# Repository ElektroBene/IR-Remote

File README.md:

# IR-Remote
## Introduction
This is a project for the course "microelectrical systems and design" in the electrical engineering and computer science studies at the Aschaffenburg University of Applied Sciences. The project will contain schematics and assembly code to build a custom infrared remote with the standard RC5 protocol.

## Schematics
- v1: basic schematic to show inputs and outputs with pic18f452
- v2: proper schematic including reset circuit, quartz oscillator and power supply
- v3: proper layout with remote design
- v4: optimize inductor width, space management and add cooling area for power supply
- v5: reroute with pwm and interrupt pins, add cooling area for battery and gnd area

## Authors
Benedikt Schnörr,
Sebastian Pasinski

### Work Packages
- schematics in v1 and v2: Benedikt
- layout in v2: Sebastian
- schematics in v3: Benedikt, Sebastian
- layout in v3: Benedikt, Sebastian
- layout in v4/5: Benedikt
- code for rc5 protocol: Benedikt

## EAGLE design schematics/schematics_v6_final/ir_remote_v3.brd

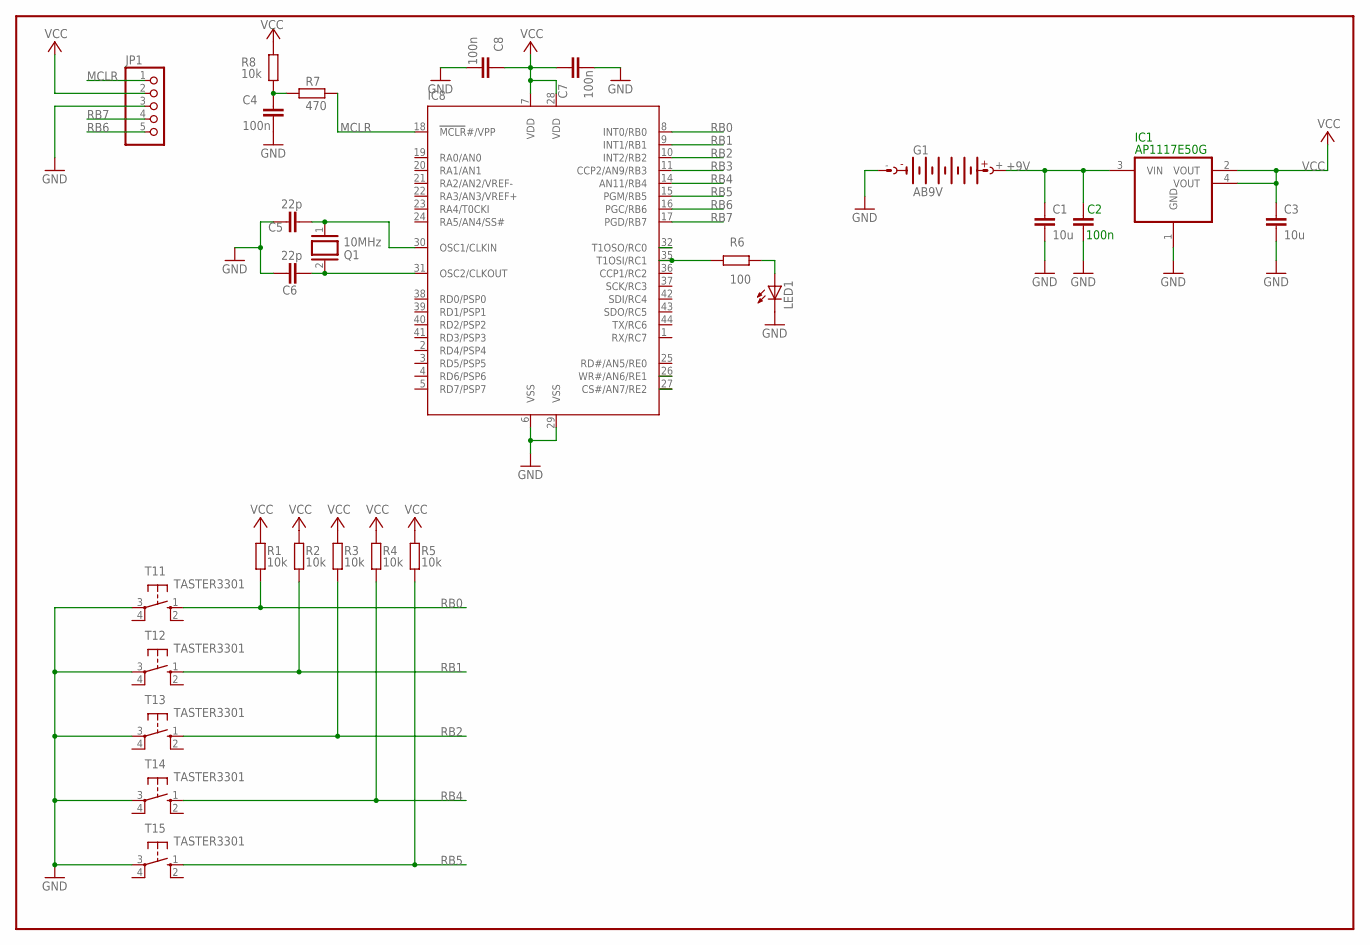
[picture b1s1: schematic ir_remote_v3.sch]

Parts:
C1, C3: 10u; C0805
C2, C4, C7, C8: 100n; C0805
C5, C6: 22p; C0603_WE
G1: AB9V
IC1: AP1117E50G; SOT223
IC8: PIC18F4520; TQFP44
JP1: PINHD-1X5; 1X05
LED1: LED5MM
Q1: 10MHz; QUARZ_HC5032/2
R1, R2, R3, R4, R5, R8: 10k; M0805
R6: 100; M0805
R7: 470; M0805
T11, T12, T13, T14, T15: TASTER3301

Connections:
+9V: C1.1, C2.1, G1.+, IC1.3 (VIN)
D0_LCD: IC8.27 (CS#/AN7/RE2)
D1_LCD: IC8.26 (WR#/AN6/RE1)
GND: C1.2, C2.2, C3.2, C4.2, C5.1, C6.1, C7.2, C8.2, G1.-, IC1.1 (GND), IC8.6 (VSS), IC8.29 (VSS), JP1.3, LED1.K (C), T11.3, T12.3, T13.3, T14.3, T15.3
MCLR: IC8.18 (MCLR#/VPP), JP1.1, R7.1
unnamed: LED1.A, R6.2
unnamed: C4.1, R7.2, R8.2
unnamed: C5.2, IC8.30 (OSC1/CLKIN), Q1.1
unnamed: C6.2, IC8.31 (OSC2/CLKOUT), Q1.2
RB0: IC8.8 (INT0/RB0), R1.2, T11.1 (S)
RB1: IC8.9 (INT1/RB1), R2.2, T12.1 (S)
RB2: IC8.10 (INT2/RB2), IC8.32 (T1OSO/RC0), R3.2, T13.1 (S)
RB3: IC8.11 (CCP2/AN9/RB3)
RB4: IC8.14 (AN11/RB4), R4.2, T14.1 (S)
RB5: IC8.15 (PGM/RB5), R5.2, T15.1 (S)
RB6: IC8.16 (PGC/RB6), JP1.5
RB7: IC8.17 (PGD/RB7), JP1.4
RC1: IC8.35 (T1OSI/RC1), R6.1
VCC: C3.1, C7.1, C8.1, IC1.2 (VOUT), IC1.4 (VOUT), IC8.7 (VDD), IC8.28 (VDD), JP1.2, R1.1, R2.1, R3.1, R4.1, R5.1, R8.1

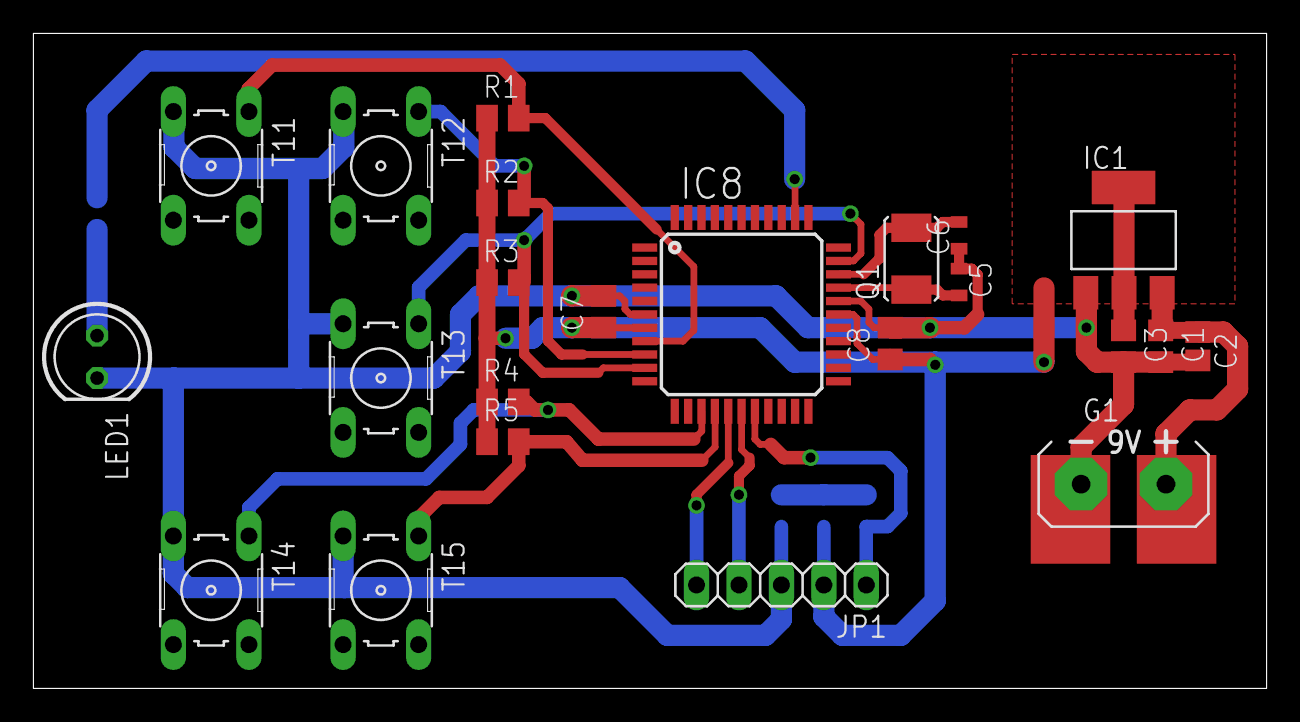
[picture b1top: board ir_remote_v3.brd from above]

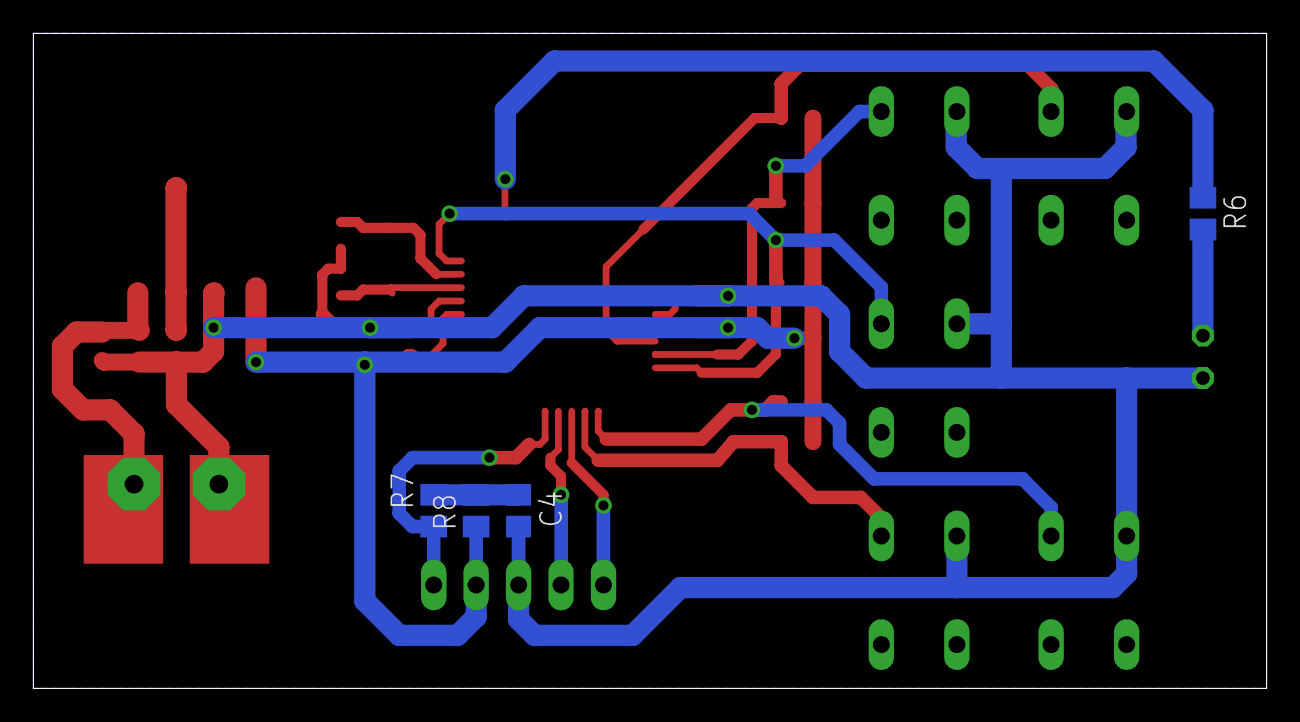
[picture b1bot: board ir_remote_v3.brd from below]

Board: 2 copper layers, 73.8 x 39.2 mm, 27 parts (4 on the bottom side), 16 nets.

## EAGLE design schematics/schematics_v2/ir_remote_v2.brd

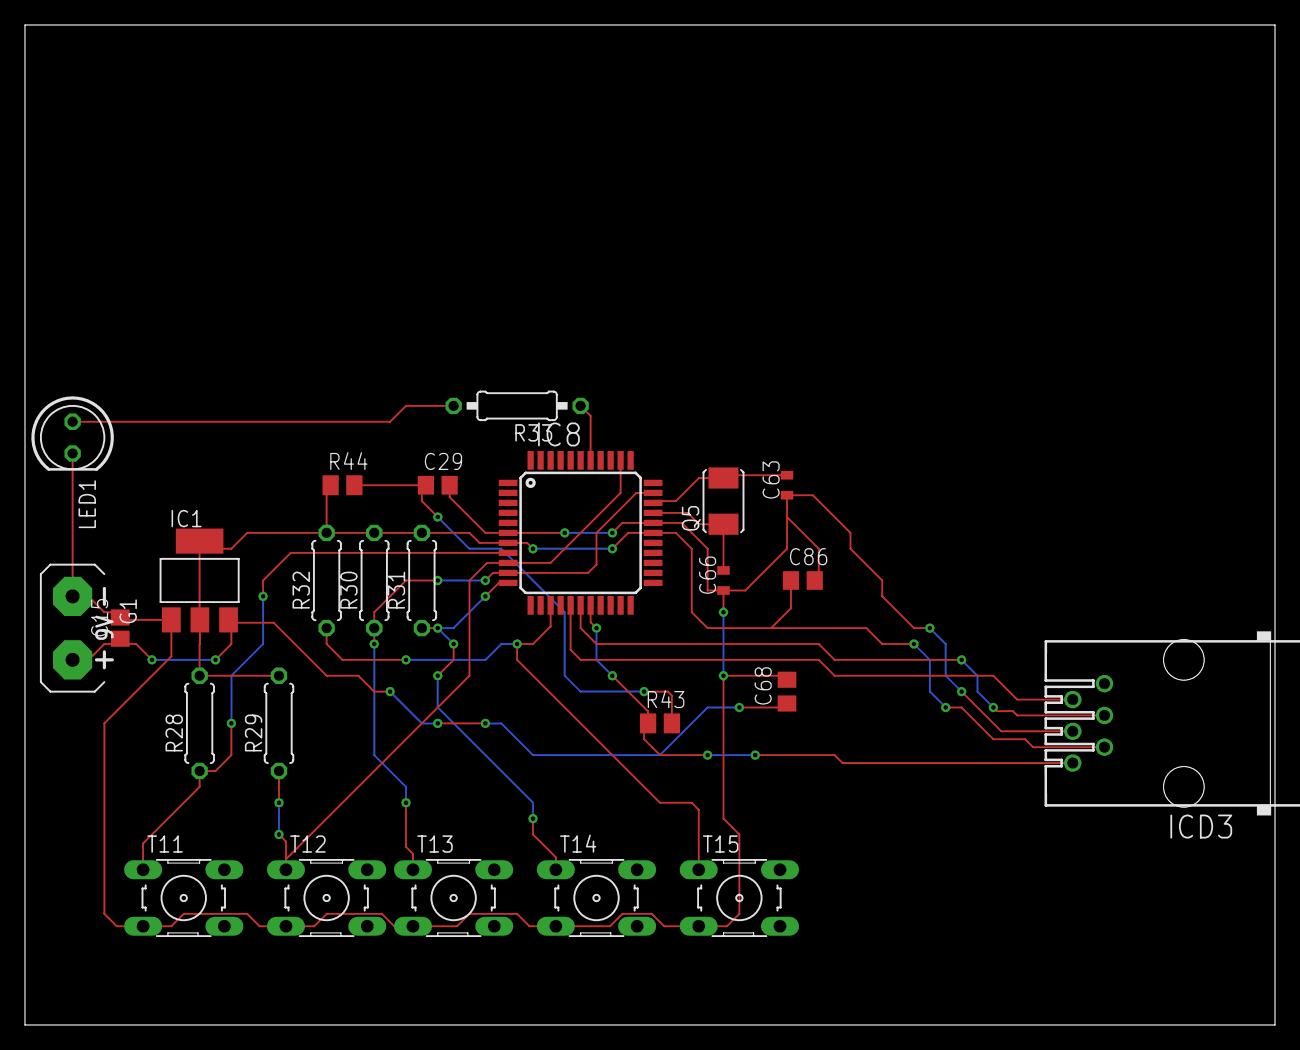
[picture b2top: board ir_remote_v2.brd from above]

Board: 2 copper layers, 100.0 x 80.0 mm, 25 parts (0 on the bottom side), 16 nets.

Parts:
C15, C29: 100n; C0805
C63, C66: 22p; C0603_WE
C68, C86: 10u; C0805
G1: AB9V
IC1: AP1117E50G; SOT223
IC8: TQFP44
ICD3: 520250-3
LED1: LED5MM
Q5: 10MHz; QUARZ_HC5032/2
R28, R29, R30, R31, R32: 10k; 0207/7
R33: 1k; 0207/10
R43: 470; M0805
R44: 10k; M0805
T11, T12, T13, T14, T15: TASTER3301

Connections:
+9V: C15.1, C68.1, G1.+, IC1.3
GND: C15.2, C29.2, C63.1, C66.1, C68.2, C86.2, G1.-, IC1.1, IC8.6, IC8.29, ICD3.3, LED1.K, T11.3, T12.3, T13.3, T14.3, T15.3
MCLR: IC8.18, ICD3.1, R43.1
unnamed: LED1.A, R33.2
unnamed: C29.1, R43.2, R44.2
unnamed: C66.2, IC8.30, Q5.1
unnamed: C63.2, IC8.31, Q5.2
RB0: IC8.8, R28.1, T11.1
RB1: IC8.9, IC8.35, R29.1, T12.1
RB2: IC8.10, IC8.32, R30.1, T13.1
RB3: IC8.11, R31.1, T14.1
RB4: IC8.14, R32.1, T15.1
RB6: IC8.16, ICD3.5
RB7: IC8.17, ICD3.4
RD0_LED: IC8.38, R33.1
VCC: C86.1, IC1.2, IC1.4, IC8.7, IC8.28, ICD3.2, R28.2, R29.2, R30.2, R31.2, R32.2, R44.1

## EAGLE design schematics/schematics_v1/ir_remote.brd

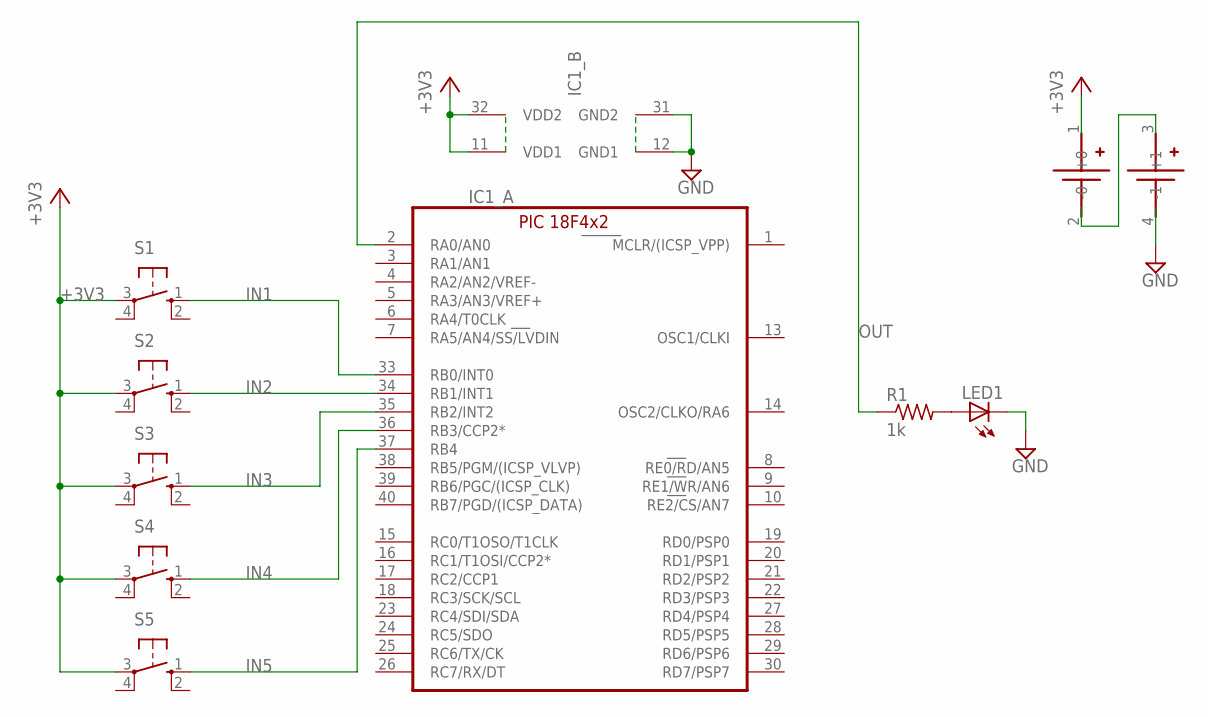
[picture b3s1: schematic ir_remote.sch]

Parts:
IC1: PIC18F4X2DIL40; DIL40
LED1: LED5MM
R1: 1k; 0207/12
S1, S2, S3, S4, S5: 10-XX; B3F-10XX
U$1: BLOSSOM-BLM-18650-2PCS

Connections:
+3V3: IC1.11 (VDD1), IC1.32 (VDD2), S1.3, S2.3, S3.3, S4.3, S5.3, U$1.1 (+0)
GND: IC1.12 (GND1), IC1.31 (GND2), LED1.K (C)
IN1: IC1.33 (RB0/INT0), S1.1 (S)
IN2: IC1.34 (RB1/INT1), S2.1 (S)
IN3: IC1.35 (RB2/INT2), S3.1 (S)
IN4: IC1.36 (RB3/CCP2*), S4.1 (S)
IN5: IC1.37 (RB4), S5.1 (S)
MCLR/(ICSP_VPP): IC1.1 (MCLR/(ICSP_VPP))
unnamed: LED1.A, R1.2
OSC1/CLKI: IC1.13 (OSC1/CLKI)
OSC2/CLKO/RA6: IC1.14 (OSC2/CLKO/RA6)
OUT: IC1.2 (RA0/AN0), R1.1

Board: 2 copper layers, 9 parts (0 on the bottom side), 9 nets, no tracks yet.

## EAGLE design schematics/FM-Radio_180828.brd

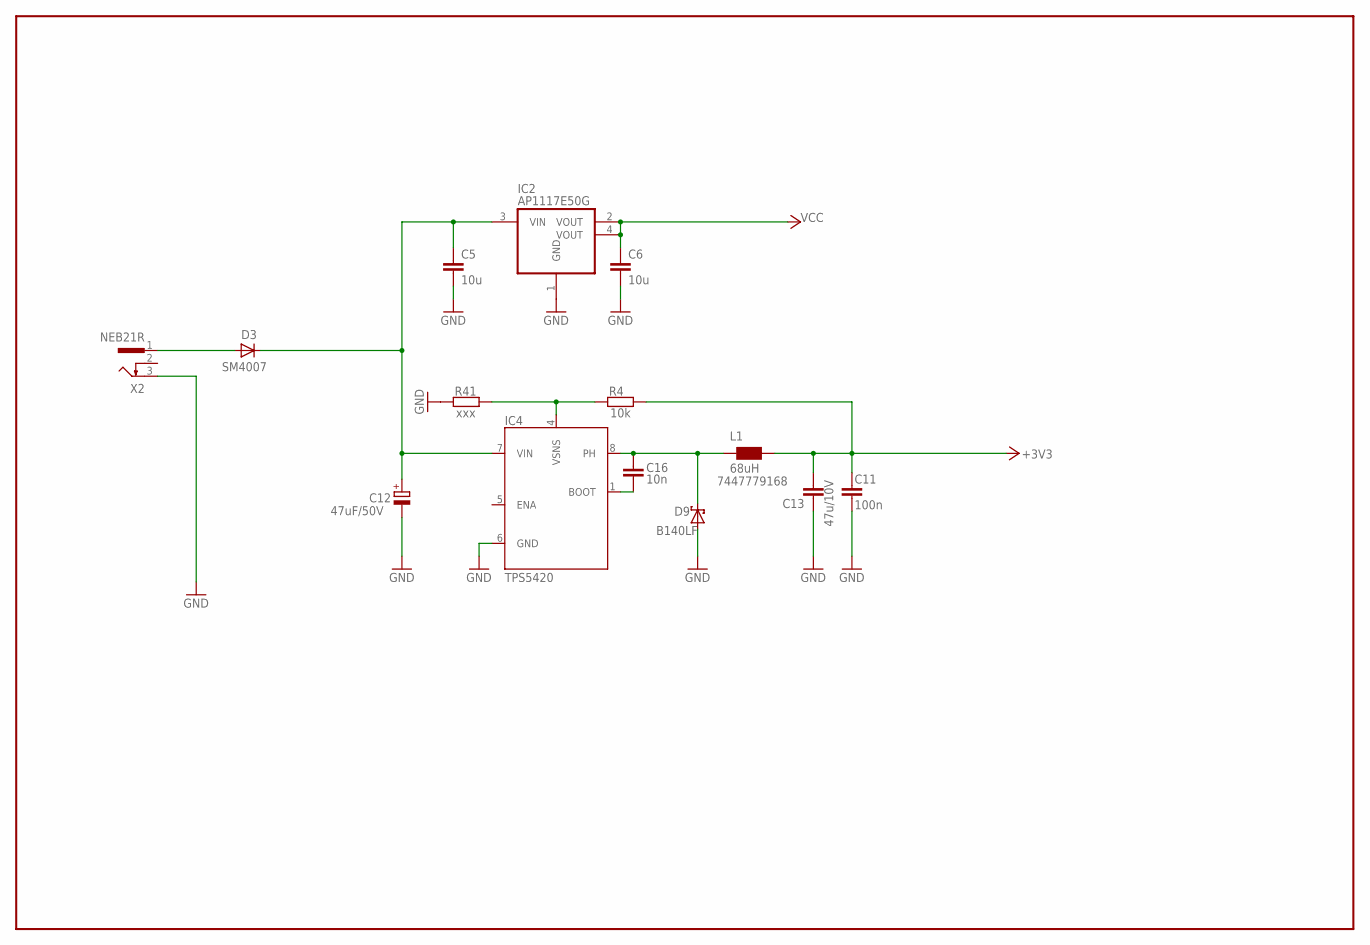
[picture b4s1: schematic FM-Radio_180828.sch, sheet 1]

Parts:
C5, C6: 10u; C0805
C11: 100n; C0805
C12: 47uF/50V; PANASONIC_D
C13: 47u/10V; C1210
C16: 10n; C0805
D3: SM4007; MELF
D9: B140LF; CD1607
IC2: AP1117E50G; SOT223
IC4: TPS5420; SO8
L1: 68uH; WE-PD_S/M
R4: 10k; R0805
R41: xxx; R0805
X2: NEB21R; FARNELL 1217037

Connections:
+3V3: C11.1, C13.1, L1.1 (2), R4.2; also elsewhere on the board
+9V: C5.1, C12.+, D3.C, IC2.3 (VIN), IC4.7 (VIN); also elsewhere on the board
GND: C5.2, C6.2, C11.2, C12.-, C13.2, D9.A, IC2.1 (GND), IC4.6 (GND), R41.1, X2.3; also elsewhere on the board
unnamed: D3.A, X2.1
unnamed: IC4.4 (VSNS), R4.1, R41.2
unnamed: C16.1, IC4.1 (BOOT)
unnamed: C16.2, D9.C, IC4.8 (PH), L1.2 (1)
VCC: C6.1, IC2.2 (VOUT), IC2.4 (VOUT); also elsewhere on the board

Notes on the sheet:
7447779168

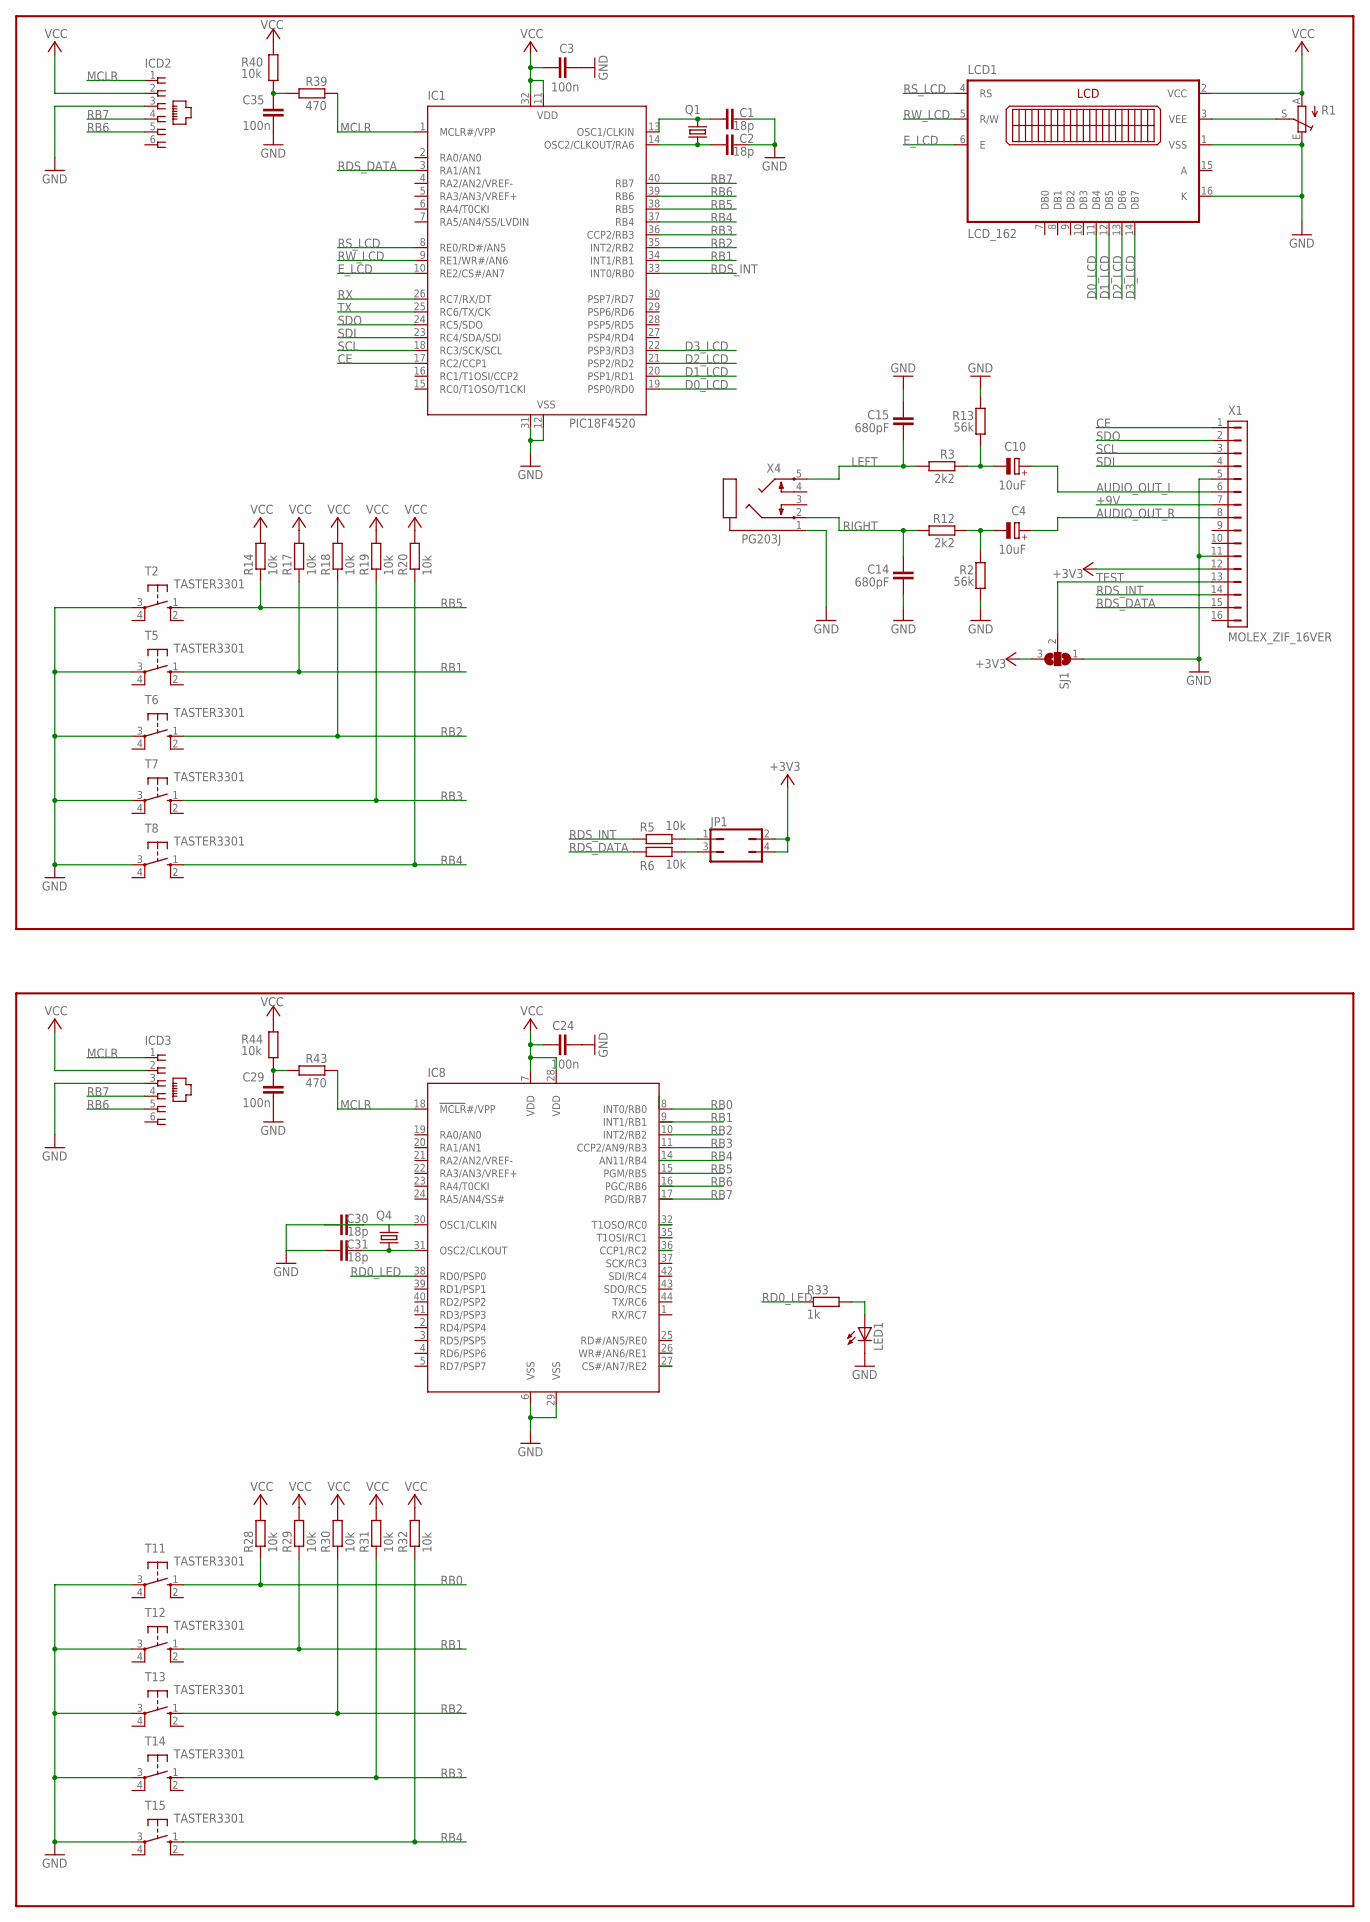
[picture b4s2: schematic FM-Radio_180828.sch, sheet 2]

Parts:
C1, C2, C30, C31: 18p; C0805
C3, C24, C29, C35: 100n; C0805
C4, C10: 10uF; TT2D4
C14, C15: 680pF; C025-025X050
IC1: PIC18F4520; DIL40
IC8: PIC18F4520; TQFP44
ICD2, ICD3: 520250-3
JP1: JP2Q
LCD1: LCD_162
LED1: LED5MM
Q1, Q4: CRYTALHC49U-V; HC49U-V
R1: TRIM_EU-LI10; LI10
R2, R13: 56k; 0207/7
R3, R12: 2k2; 0207/7
R5, R6, R40, R44: 10k; M0805
R14, R17, R18, R19, R20, R28, R29, R30, R31, R32: 10k; 0207/7
R33: 1k; 0207/10
R39, R43: 470; M0805
SJ1: SJ2W; SJ_2
T2, T5, T6, T7, T8, T11, T12, T13, T14, T15: TASTER3301
X1: MOLEX_ZIF_16VER; ZIF_16POL
X4: PG203J

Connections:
+3V3: JP1.2, JP1.4, SJ1.3, X1.12; also elsewhere on the board
+9V: X1.7; also elsewhere on the board
AUDIO_OUT_L: C10.+, X1.6; also elsewhere on the board
AUDIO_OUT_R: C4.+, X1.8; also elsewhere on the board
CE: IC1.17 (RC2/CCP1), X1.1; also elsewhere on the board
D0_LCD: IC1.19 (PSP0/RD0), IC8.27 (CS#/AN7/RE2), LCD1.11 (DB4); also elsewhere on the board
D1_LCD: IC1.20 (PSP1/RD1), IC8.26 (WR#/AN6/RE1), LCD1.12 (DB5); also elsewhere on the board
D2_LCD: IC1.21 (PSP2/RD2), LCD1.13 (DB6); also elsewhere on the board
D3_LCD: IC1.22 (PSP3/RD3), LCD1.14 (DB7); also elsewhere on the board
E_LCD: IC1.10 (RE2/CS#/AN7), LCD1.6 (E); also elsewhere on the board
GND: C1.2, C2.2, C3.2, C14.1, C15.2, C24.2, C29.2, C30.1, C30.2, C31.1, C35.2, IC1.12 (VSS), IC1.31 (VSS), IC8.6 (VSS), IC8.30 (OSC1/CLKIN), ICD2.3, ICD3.3, LCD1.1 (VSS), LCD1.16 (K), LED1.K (C), Q4.2, R1.E, R2.2, R13.1, SJ1.1, T2.3, T5.3, T6.3, T7.3, T8.3, T11.3, T12.3, T13.3, T14.3, T15.3, X1.5, X1.11, X4.1; also elsewhere on the board
LEFT: C15.1, R3.1, X4.5; also elsewhere on the board
MCLR: IC1.1 (MCLR#/VPP), IC8.18 (MCLR#/VPP), ICD2.1, ICD3.1, R39.1, R43.1; also elsewhere on the board
unnamed: C10.-, R3.2, R13.2
unnamed: JP1.1, R5.2
unnamed: JP1.3, R6.2
unnamed: C2.1, IC1.14 (OSC2/CLKOUT/RA6), Q1.1
unnamed: C1.1, IC1.13 (OSC1/CLKIN), Q1.2
unnamed: LCD1.3 (VEE), R1.S
unnamed: C4.-, R2.1, R12.2
unnamed: LED1.A, R33.2
unnamed: C29.1, R43.2, R44.2
unnamed: C31.2, IC8.31 (OSC2/CLKOUT), Q4.1
unnamed: C35.1, R39.2, R40.2
RB0: IC8.8 (INT0/RB0), R28.1, T11.1 (S)
RB1: IC1.34 (INT1/RB1), IC8.9 (INT1/RB1), IC8.35 (T1OSI/RC1), R17.1, R29.1, T5.1 (S), T12.1 (S); also elsewhere on the board
RB2: IC1.35 (INT2/RB2), IC8.10 (INT2/RB2), IC8.32 (T1OSO/RC0), R18.1, R30.1, T6.1 (S), T13.1 (S); also elsewhere on the board
RB3: IC1.36 (CCP2/RB3), IC8.11 (CCP2/AN9/RB3), R19.1, R31.1, T7.1 (S), T14.1 (S); also elsewhere on the board
RB4: IC1.37 (RB4), IC8.14 (AN11/RB4), R20.1, R32.1, T8.1 (S), T15.1 (S); also elsewhere on the board
RB5: IC1.38 (RB5), IC8.15 (PGM/RB5), R14.1, T2.1 (S); also elsewhere on the board
RB6: IC1.39 (RB6), IC8.16 (PGC/RB6), ICD2.5, ICD3.5; also elsewhere on the board
RB7: IC1.40 (RB7), IC8.17 (PGD/RB7), ICD2.4, ICD3.4; also elsewhere on the board
RD0_LED: IC8.38 (RD0/PSP0), R33.1
RDS_DATA: IC1.3 (RA1/AN1), R6.1, X1.15; also elsewhere on the board
RDS_INT: IC1.33 (INT0/RB0), IC8.36 (CCP1/RC2), R5.1, X1.14; also elsewhere on the board
RIGHT: C14.2, R12.1, X4.2; also elsewhere on the board
RS_LCD: IC1.8 (RE0/RD#/AN5), LCD1.4 (RS); also elsewhere on the board
RW_LCD: IC1.9 (RE1/WR#/AN6), LCD1.5 (R/W); also elsewhere on the board
RX: IC1.26 (RC7/RX/DT); also elsewhere on the board
SCL: IC1.18 (RC3/SCK/SCL), X1.3; also elsewhere on the board
SDI: IC1.23 (RC4/SDA/SDI), X1.4; also elsewhere on the board
SDO: IC1.24 (RC5/SDO), X1.2; also elsewhere on the board
TEST: SJ1.2, X1.13; also elsewhere on the board
TX: IC1.25 (RC6/TX/CK); also elsewhere on the board
VCC: C3.1, C24.1, IC1.11 (VDD), IC1.32 (VDD), IC8.7 (VDD), ICD2.2, ICD3.2, LCD1.2 (VCC), R1.A, R14.2, R17.2, R18.2, R19.2, R20.2, R28.2, R29.2, R30.2, R31.2, R32.2, R40.1, R44.1; also elsewhere on the board

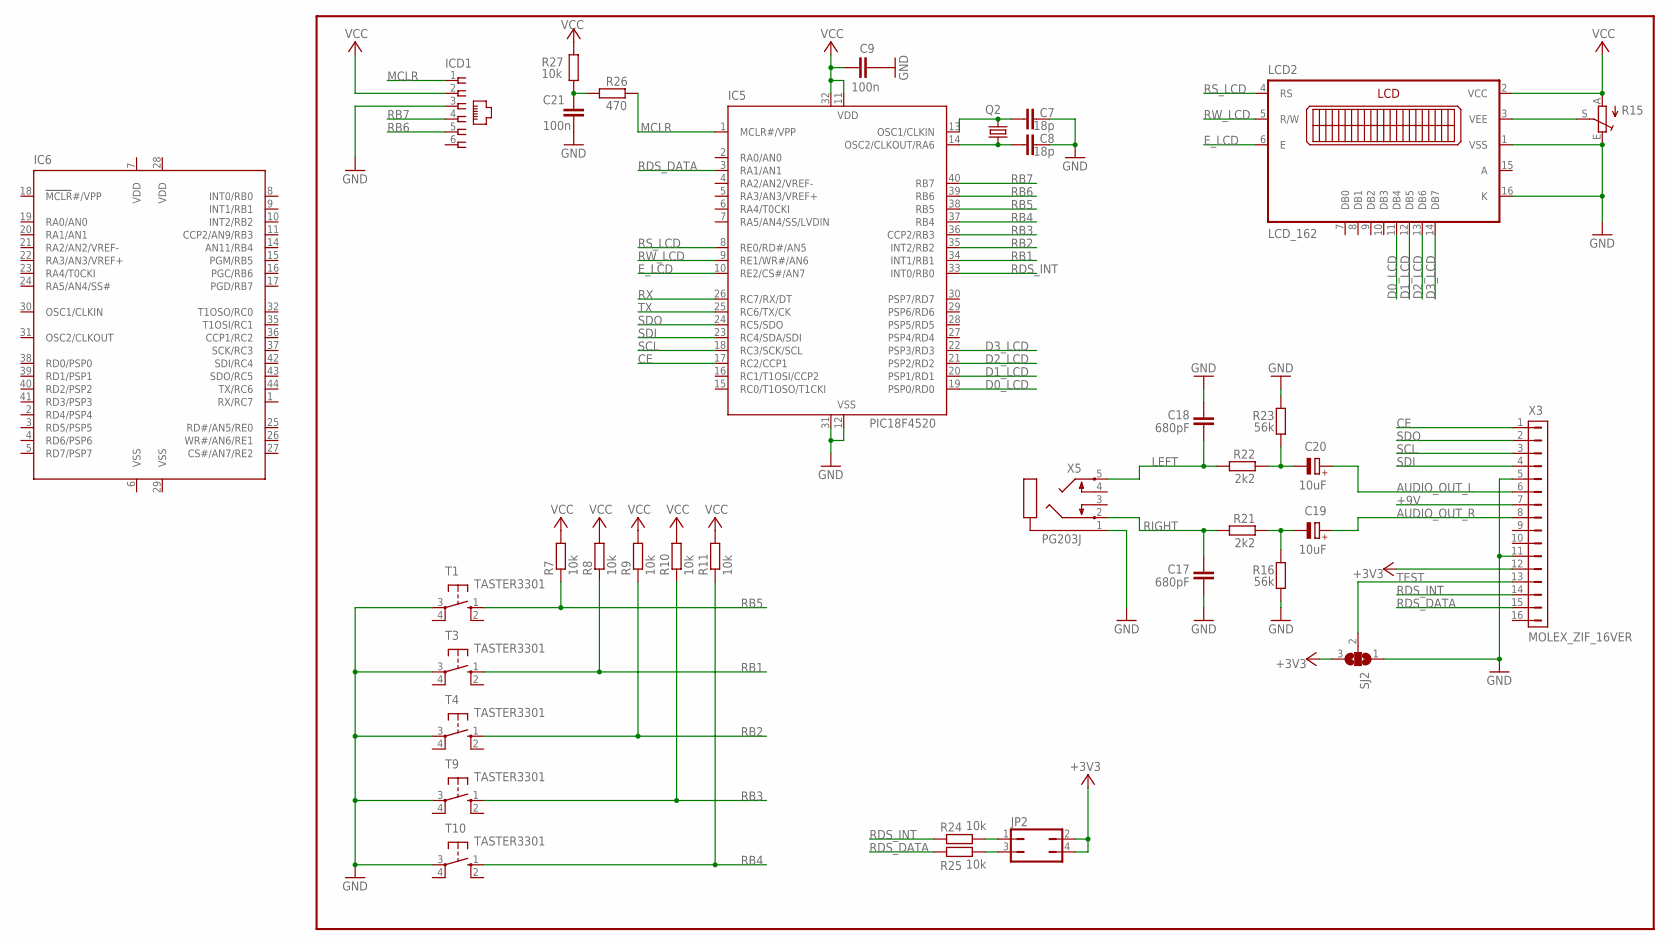
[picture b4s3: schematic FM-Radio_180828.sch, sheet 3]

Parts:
C7, C8: 18p; C0805
C9, C21: 100n; C0805
C17, C18: 680pF; C025-025X050
C19, C20: 10uF; TT2D4
IC5: PIC18F4520; DIL40
IC6: PIC18F4520; TQFP44
ICD1: 520250-3
JP2: JP2Q
LCD2: LCD_162
Q2: CRYTALHC49U-V; HC49U-V
R7, R8, R9, R10, R11: 10k; 0207/7
R15: TRIM_EU-LI10; LI10
R16, R23: 56k; 0207/7
R21, R22: 2k2; 0207/7
R24, R25, R27: 10k; M0805
R26: 470; M0805
SJ2: SJ2W; SJ_2
T1, T3, T4, T9, T10: TASTER3301
X3: MOLEX_ZIF_16VER; ZIF_16POL
X5: PG203J

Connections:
+3V3: JP2.2, JP2.4, SJ2.3, X3.12; also elsewhere on the board
+9V: X3.7; also elsewhere on the board
AUDIO_OUT_L: C20.+, X3.6; also elsewhere on the board
AUDIO_OUT_R: C19.+, X3.8; also elsewhere on the board
CE: IC5.17 (RC2/CCP1), X3.1; also elsewhere on the board
D0_LCD: IC5.19 (PSP0/RD0), LCD2.11 (DB4); also elsewhere on the board
D1_LCD: IC5.20 (PSP1/RD1), LCD2.12 (DB5); also elsewhere on the board
D2_LCD: IC5.21 (PSP2/RD2), LCD2.13 (DB6); also elsewhere on the board
D3_LCD: IC5.22 (PSP3/RD3), LCD2.14 (DB7); also elsewhere on the board
E_LCD: IC5.10 (RE2/CS#/AN7), LCD2.6 (E); also elsewhere on the board
GND: C7.2, C8.2, C9.2, C17.1, C18.2, C21.2, IC5.12 (VSS), IC5.31 (VSS), ICD1.3, LCD2.1 (VSS), LCD2.16 (K), R15.E, R16.2, R23.1, SJ2.1, T1.3, T3.3, T4.3, T9.3, T10.3, X3.5, X3.11, X5.1; also elsewhere on the board
LEFT: C18.1, R22.1, X5.5; also elsewhere on the board
MCLR: IC5.1 (MCLR#/VPP), ICD1.1, R26.1; also elsewhere on the board
unnamed: C8.1, IC5.14 (OSC2/CLKOUT/RA6), Q2.1
unnamed: C7.1, IC5.13 (OSC1/CLKIN), Q2.2
unnamed: LCD2.3 (VEE), R15.S
unnamed: C20.-, R22.2, R23.2
unnamed: C19.-, R16.1, R21.2
unnamed: JP2.1, R24.2
unnamed: JP2.3, R25.2
unnamed: C21.1, R26.2, R27.2
RB1: IC5.34 (INT1/RB1), R8.1, T3.1 (S); also elsewhere on the board
RB2: IC5.35 (INT2/RB2), R9.1, T4.1 (S); also elsewhere on the board
RB3: IC5.36 (CCP2/RB3), R10.1, T9.1 (S); also elsewhere on the board
RB4: IC5.37 (RB4), R11.1, T10.1 (S); also elsewhere on the board
RB5: IC5.38 (RB5), R7.1, T1.1 (S); also elsewhere on the board
RB6: IC5.39 (RB6), ICD1.5; also elsewhere on the board
RB7: IC5.40 (RB7), ICD1.4; also elsewhere on the board
RDS_DATA: IC5.3 (RA1/AN1), R25.1, X3.15; also elsewhere on the board
RDS_INT: IC5.33 (INT0/RB0), R24.1, X3.14; also elsewhere on the board
RIGHT: C17.2, R21.1, X5.2; also elsewhere on the board
RS_LCD: IC5.8 (RE0/RD#/AN5), LCD2.4 (RS); also elsewhere on the board
RW_LCD: IC5.9 (RE1/WR#/AN6), LCD2.5 (R/W); also elsewhere on the board
RX: IC5.26 (RC7/RX/DT); also elsewhere on the board
SCL: IC5.18 (RC3/SCK/SCL), X3.3; also elsewhere on the board
SDI: IC5.23 (RC4/SDA/SDI), X3.4; also elsewhere on the board
SDO: IC5.24 (RC5/SDO), X3.2; also elsewhere on the board
TEST: SJ2.2, X3.13; also elsewhere on the board
TX: IC5.25 (RC6/TX/CK); also elsewhere on the board
VCC: C9.1, IC5.11 (VDD), IC5.32 (VDD), ICD1.2, LCD2.2 (VCC), R7.2, R8.2, R9.2, R10.2, R11.2, R15.A, R27.1; also elsewhere on the board

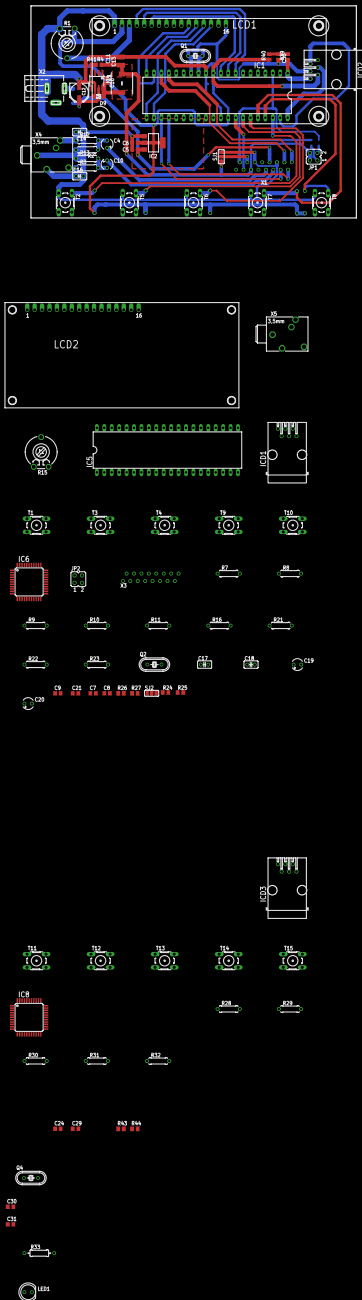
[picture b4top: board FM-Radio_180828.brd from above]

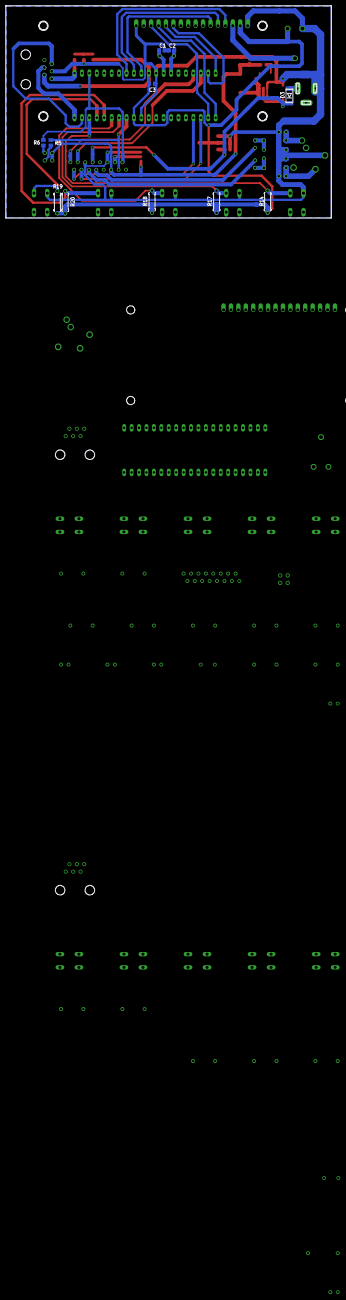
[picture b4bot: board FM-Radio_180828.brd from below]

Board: 2 copper layers, 111.3 x 72.5 mm, 110 parts (11 on the bottom side), 57 nets.

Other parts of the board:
U$3, U$4, U$5, U$7: 3,2

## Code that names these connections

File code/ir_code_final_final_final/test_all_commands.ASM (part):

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							; interrupts
		return

; send stop command with pin RB0
send_rb_0:
		bsf skip_release,0	; set skip_release<0> to prevent skipping this
							; command
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							; interrupts
		return

; send forward command with pin RB1
send_rb_1:
		bsf skip_release,0	; set skip_release<0> to prevent skipping this
							; command
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							; interrupts
		return

; send play/pause command with pin RB2
send_rb_2:
		bsf skip_release,0	; set skip_release<0> to prevent skipping this
							; command
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							; interrupts
		return
		
; send mute command with pin RB4
send_rb_4:
		movlw b'00110101'	; move rc5 code for play command to bit buffer
		movwf bit_buffer_h
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init_portc:
		clrf PORTC			; reset port c and its latch
		clrf LATC
		movlw b'11111101'	; set pin RC1 to be output, all other RC pins to be
		movwf TRISC			; inputs
		return
		
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
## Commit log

2024-03-27 Add first basic schematic
2024-03-27 Modify directory structure
2024-03-27 Add new schematics
2024-03-27 Add schematic_v2 including proper pic model, reset circuit, oscillator and power supply
2024-03-27 Modify power supply with AP1117E50G replacing LM7805
2024-03-27 Add first report
2024-04-03 Add files via upload
    Exchanging the Quartz on the Microcontroller
2024-04-03 Add files via upload
    First placing of the components in layout, no proper connection, supply currents nor ground
2024-04-06 Create board
2024-04-06 Add files via upload
    First placing of components and first wire
2024-04-07 Add files via upload
    First Layout - 12 DR - Errors
2024-04-08 Add files via upload
    PCB Layout - Fixed Design Rules, no recommendation from Volpe/Wegmann
2024-04-09 Create schematics_v3
2024-04-09 Add version 3 schematics including basic layout and improved circuitry
2024-04-09 Update circuit layout
2024-04-09 Add files via upload
    Connected Components _1
2024-04-13 Clean up files in schematics v2
2024-04-14 Add files via upload
    Eagle Seminar with design tips, rules etc. for pcb layout
2024-04-16 Fix project directory structure
2024-04-17 Add files via upload
    IR-Remote Layout
2024-04-20 Add files via upload
    Voltage Ragulator with cooling area on VCC option 1, can be varried and be turned
    Unknown whether the second capacitance c4 is needed nearer by the microcontroller
2024-04-21 Add files via upload
    ir_remote v3 cooling area patch of ic3
2024-04-22 Add schematics v4 with layout optimization
2024-04-22 Improve schematics v4
2024-04-23 Add schematics v5 directory structure
2024-04-23 Add schematics and layout for v5 including coupling caps and minor layout changes
2024-04-26 Add schematics v5.2
2024-05-04 Add minor modifications including ground and battery areas
2024-05-04 Add minor changes to layout v5_3
2024-05-05 Add pic datasheet and layout images
2024-05-07 Add third report
2024-05-07 Add bill of materials
2024-05-08 Update config_int.asm
    schaltet aber nur led 1,2 an
2024-05-11 Update config_int.asm
    Add con anpassung und reihen folge int
2024-05-11 Update config_int.asm
    ISR, changing order of clearing flag bit
2024-05-13 Test pwm code
2024-05-15 Update config_int.asm
    Das Programm schaltet leds an und geht in den interrupt nur kann der Pin wert nicht zuverlässig ausgelesen werden
2024-05-16 Add dimensions for schematics v5.3
2024-05-21 Add pwm
2024-05-22 Add final schematics and layout v6
2024-05-23 Add sender for rc5 signal with pwm on timer 2 and half bit with timer 0
2024-06-02 Add files via upload
    Final schematics, correcting some basic errors
2024-06-02 Add files via upload
    All Pins on PortB enabled as interrupts, needs to be tested
2024-06-02 Add files via upload
    Int 0 - 2 as high interrupts, interrupts 1&2 need to be tested, no software polling to find out what pin caused interrupt
2024-06-04 Add main code files
2024-06-04 Add code to send pic to sleep and wake up again with high priority service interrupt routine
2024-06-05 Update INT-2&RBonChange.txt
    Addeted Interface for sending commands, not compiled, not tested, and no sendcommands
2024-06-05 Update INT-2&RBonChange.txt
    Schnittstelle iengefügt, kann aber kein Taster interrupt beim demoboard auslösen, hardware??
2024-06-06 Add prototype for full asm code in code/ir_remote_main_code directory
2024-06-13 Test algorithm and emulate longer button press
2024-06-14 Add toggle bit
2024-06-14 Initial commit in feature_button_press branch
2024-06-14 Try longer button presses (still in development)
2024-06-16 Add tests for ir remote board.
2024-06-17 Add report 4, 5 and 6 to doc directory
2024-06-18 Add pwm pulse with correct frequency and 32 single pulses
2024-06-18 Add button interrupt to start pwm pulses
2024-06-18 Add most of the working code so that buttons send command
2024-06-21 It f*king works!
2024-06-25 Add test files for final remote tests
2024-06-26 Include all commands
2024-06-26 Add possible error sources in code test_final_remote
2024-06-27 All commands f*king work :)
2024-06-27 Add toggle bit to all commands (not working yet)
2024-06-29 Add final working code in ir_code_final_project directory
2024-06-29 Make code look pretty :)
2024-06-29 Add comments in code. This will be the last tested version of this code. When all falls apart, this will be the last checkpoint.
2024-06-29 Finish code with comments and prettier form. This code may fail, in this case, the previous commit should be used as checkpoint.
2024-06-30 Update test_all_commands.ASM
    high int: deleted unnecessary interrupt flag clearing
2024-06-30 Update test_all_commands.ASM
    explanation to retfie command
2024-07-01 Add final working code. This is the final tested version 1.0.0.
2024-07-01 Add first draft for final report
2024-07-01 Add final version for final report
2024-07-02 Add final touches to doc
